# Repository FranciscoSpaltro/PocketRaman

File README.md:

# PocketRaman
Low-cost portable Raman spectrometer prototype developed at SUPSI. Based on Raspberry Pi 4 and STM32F469I-DISCO, using a TCD1304 linear CCD with ADC and DMA-based acquisition. Includes custom 3D-printed mechanical parts to reuse optical mounting components and reduce cost.

## Status

This project implements a first working pipeline for CCD readout using:
- Timer-driven ADC sampling with DMA
- UART DMA streaming to host
- Python-based real-time visualization

Data acquisition and transmission are functional.
Frame synchronization relative to ICG/SH is currently under refinement,
which may cause horizontal drift in the displayed signal.

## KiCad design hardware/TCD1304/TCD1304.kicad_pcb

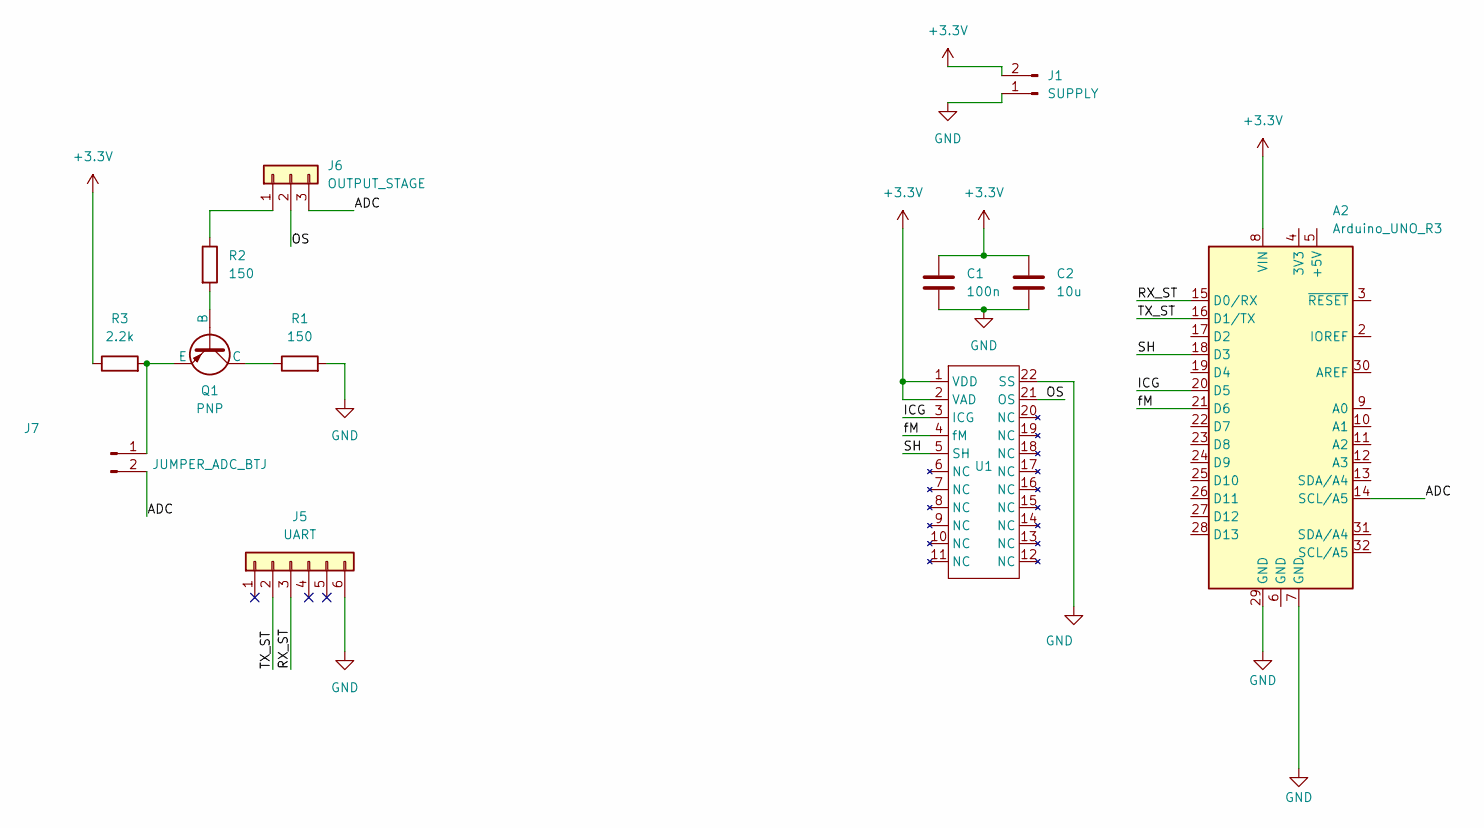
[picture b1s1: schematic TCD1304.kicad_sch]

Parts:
A2: Arduino_UNO_R3
C1: 100n; C_0805_2012Metric_Pad1.18x1.45mm_HandSolder
C2: 10u; C_0805_2012Metric_Pad1.18x1.45mm_HandSolder
J1: SUPPLY; PinHeader_1x02_P2.54mm_Vertical
J5: UART; PinHeader_1x06_P2.54mm_Vertical
J6: OUTPUT_STAGE; PinHeader_1x03_P2.54mm_Vertical
J7: JUMPER_ADC_BTJ; PinHeader_1x02_P2.54mm_Vertical
Q1: PNP; TO18
R1, R2: 150; R_0805_2012Metric_Pad1.20x1.40mm_HandSolder
R3: 2.2k; R_0805_2012Metric_Pad1.20x1.40mm_HandSolder
U1: DIP1016W62P254L4160H372Q22N

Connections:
+3.3V: A2.8 (VIN), C1.1, C2.1, J1.2, R3.1, U1.1 (VDD), U1.2 (VAD)
/ADC: A2.14 (SCL/A5), J6.3, J7.2
/ICG: A2.20 (D5), U1.3 (ICG)
/OS: J6.2, U1.21 (OS)
/RX_ST: A2.15 (D0/RX), J5.3
/SH: A2.18 (D3), U1.5 (SH)
/TX_ST: A2.16 (D1/TX), J5.2
/fM: A2.21 (D6), U1.4 (fM)
GND: A2.7 (GND), A2.29 (GND), C1.2, C2.2, J1.1, J5.6, R1.2, U1.22 (SS)
unnamed: J6.1, R2.1
unnamed: J7.1, Q1.3 (E), R3.2
unnamed: Q1.2 (B), R2.2
unnamed: Q1.1 (C), R1.1

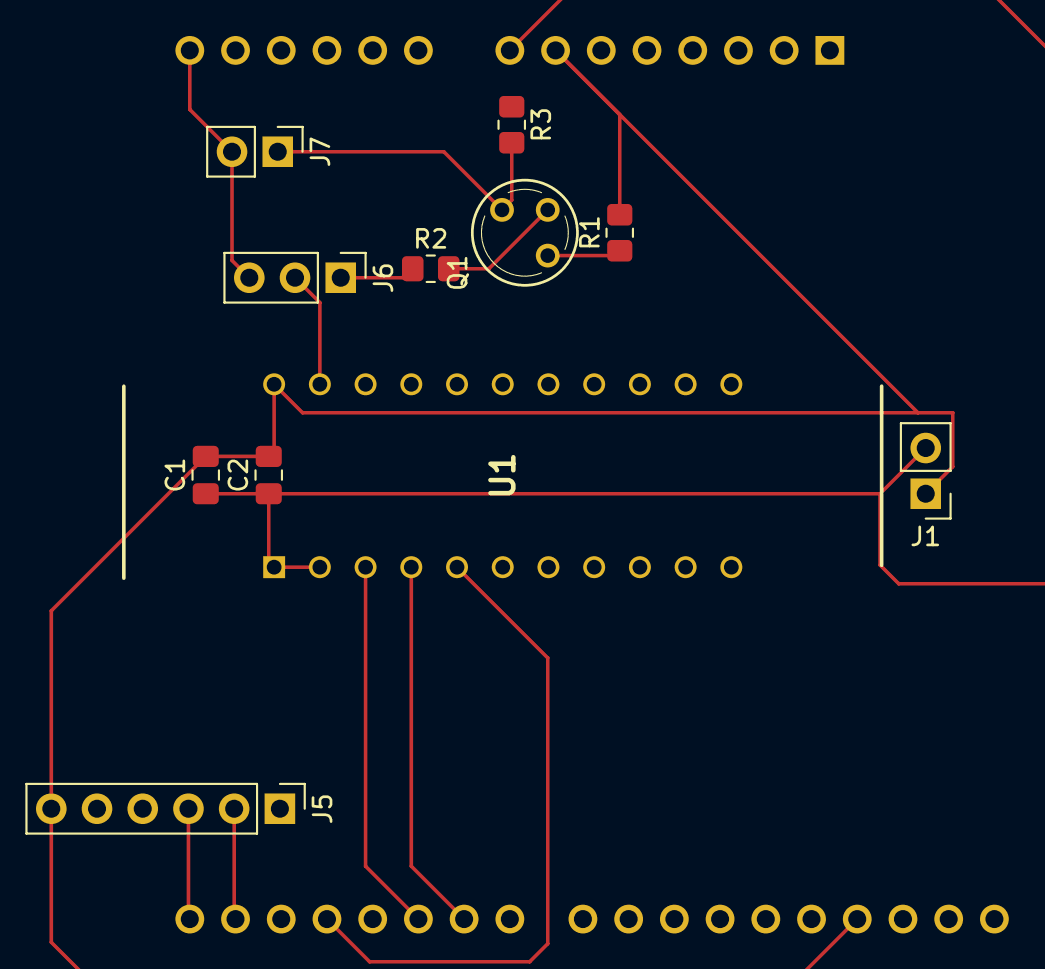
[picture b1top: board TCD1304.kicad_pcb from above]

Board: 2 copper layers, 12 parts (1 on the bottom side), 13 nets.

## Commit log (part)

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2025-12-22 Initial CCD acquisition and UART streaming (sync refinement pending)
2025-12-22 WIP: frame sync via ICG + twin timer (OC-based), ADC aligned but frame length not final
2025-12-22 Implement CCD timing sync: ICG, fM, and ADC phase-locked (v1)
    - TIM2 configured as ICG (frame timing)
    - TIM3 configured as fM (pixel clock)
    - TIM4 configured as ADC trigger, phase-locked to fM
    - TIM5 configured as SH (period), triggered by ICG
    ADC sampling time set to 28 cycles to reduce step artifacts.
    This is a first functional version; further tuning is expected.
2026-01-09 Add timer-driven state machine experiment [non-functional]
2026-01-13 Refactor CCD timing generation using TIM2 OC + DMA
    Major architectural change to generate SH and ICG signals using TIM2 in Output Compare Toggle mode driven by DMA. This replaces manual control to ensure precise, jitter-free timing.
    Key changes:
    - Implemented TIM2 + DMA circular buffer logic for signal generation.
    - Added `START_OFFSET` to prevent race conditions at t=0 and ensure SH/ICG synchronization.
    - Implemented `calculate_times` and `build_SH_table` to dynamically calculate the number of cleaning pulses (n) based on integration time using integer math.
    - Switched to static "worst-case" buffer allocation (MAX_EDGES) to avoid dynamic memory usage.
2026-01-13 Feat: Implement synchronized fM (TIM3) with phase-lock padding
    Implemented Master Clock (fM) generation and synchronized it with the Control Signals (SH/ICG) to ensure deterministic timing.
    Key Changes:
    - Master-Slave Configuration: Configured TIM2 (SH/ICG) as Master and TIM3 (fM) as Slave in Trigger Mode. Both timers now start on the exact same clock cycle, eliminating startup jitter.
    - Phase Alignment (t_4 datasheet =0): Updated START_OFFSET to 22 ticks. This aligns the ICG rising edge precisely with the fM falling edge.
    - Dynamic Phase Locking: Implemented a padding algorithm in calculate_times:
    - Calculates the remainder of the total frame duration relative to the fM period (45 tick
2026-01-13 feat: Implement CCD capture with 4x oversampling and visualization fix
    STM32 Firmware:
    - Configured TIM3 for master clock (fM) generation.
    - Implemented ADC control triggered on the ICG rising edge (TIM2 Callback).
    - Enabled NVIC interrupts for ADC1 (Stream 0) and UART6 (Stream 6).
    - Implemented buffer with fixed synchronization Header (0x4652, 0x414E...).
    - Enabled UART transmission at 460800 baud with 4x oversampling.
2026-01-14 Esta version es tecnicamente incorrecta pero funciona, por eso la guardo
2026-01-14 Implementation of prescaler by overrun and remove 1/4 frames to stabilize
2026-01-14 feat: add UART handshake synchronization and remote integration time change command
2026-01-14 More ways to graphic
2026-01-16 change header size, introduce TYPE field, cleanedcleaning up communication functions
2026-01-19 fix: dynamic integration time and frame noise
    - Fixed logic in `setup_timer_icg_sh` and main loop to ensure correct signal polarity and counter reset when changing integration time.
    - Added `END_BUFFER` to valid frames to filter out incomplete transmissions (noise).
2026-01-20 temp: remove checksum verification from data sending until fix
2026-01-20 temp: dummy test - possible source of the problem: access to adc_buffer
2026-01-21 temp: double-buffer implementation, previous to use SDRAM
2026-01-21 temp: SDRAM version with blocking UART, only with number_of_acc, no free-shooting
2026-01-21 DMA and SDRAM version with number_of_acc, no free-shooting
2026-01-22 data_accumulation and free_shooting, both without DMA, cleaner versions - work
2026-01-23 add more cmds: set_number_acc and free_shooting_enable; processing flag not implemented
2026-01-26 change comments
2026-01-26 modif constant values for external clock TIM3 (TIM2) - it needs cleaning
2026-01-26 implemention of TIM4 as ADC's clock; Python graph with bias correction
2026-01-26 implement is_flushing, specially for accumulation mode; move all variables to tcd_variables.c (preliminary)
2026-01-26 back-up before refactoring callbacks functions
2026-01-26 Clean-up variables
2026-01-26 reorganize folder firmware
2026-01-26 update directories
2026-01-27 refactor: clean-up all code, change variable location, secure extern variable declaration, remove function for icg_table (constant)
2026-01-28 start: pcb for tcd and output stage, mounting design for soft grip
2026-01-29 pcb prototype
2026-01-29 fix accumulated data sending error, separation of sending and parameter settings logic
2026-01-29 Refactoring: modularization of the Python code, creation of the spectrometer class and basic main; validations and further development remain
2026-01-30 add Altium project (start)
2026-02-09 backup before converting sch into hierarchical design
2026-02-11 update hierarchical sheet PCB and complete circuit
2026-02-17 update SCHEMATICS - added a4988 support and general redesign
2026-02-17 starting PCB placement
2026-03-03 complete first version of PCB - without protection diodes in LDO
2026-03-05 voltage devisor + buffer as TCD output signal
2026-03-05 separation of motor-peltier drivers
2026-03-06 redesign pcb, split motor stage and logic stage in two complementary pcbs
2026-03-17 update pcb, change trigger adc from tim4 to tim1
2026-03-17 new version TCD template created for testing the new pin distribution
2026-03-17 update new version firmware - TIM1 PWM CH1 and CH1N (for testing)
2026-03-27 PCB v4, separate boards + polygons; firmware adapted to migrate to STM32f446
2026-03-30 cleaning of code, backup before changes
2026-04-01 Create PCB5 with new AGND path around OS
2026-04-20 PCB: correct vias, add multiple power vias, add gnd background, add snubber for peltier
2026-04-27 split of pcb a-b; update routing; addition of real caps; rev version 1
2026-04-27 minimal changes in capacitors sch
2026-04-28 final details before Andrea's review
2026-04-28 modified with Andrea's initial corrections
2026-04-28 final corrections before Daniele's review
2026-04-30 final details before quote; add BOM
2026-04-30 PCB B ready, PCB A needs minimal corrections (EUROCIRCUITS)
2026-05-04 final changes of PCB CHECKER (EUROCIRCUITS).- Production version 1.0
2026-05-04 Last version with the updates that are in the EuroCircuit cart
2026-05-05 added some capacitors on the PCB B - final version
2026-06-01 starting some examples about processing
2026-06-05 update new version of firmware for migration; TCD signals and OS OK
2026-06-08 firmware v1, sending data with only one buffer (and discarding the rest of conversions
2026-06-09 new version with working time and accum settings
2026-06-15 create GUI v1
2026-06-16 change on RX (without DMA to separate the workflow betwwen RX and TX)
2026-06-16 fix reading data + ACK service
